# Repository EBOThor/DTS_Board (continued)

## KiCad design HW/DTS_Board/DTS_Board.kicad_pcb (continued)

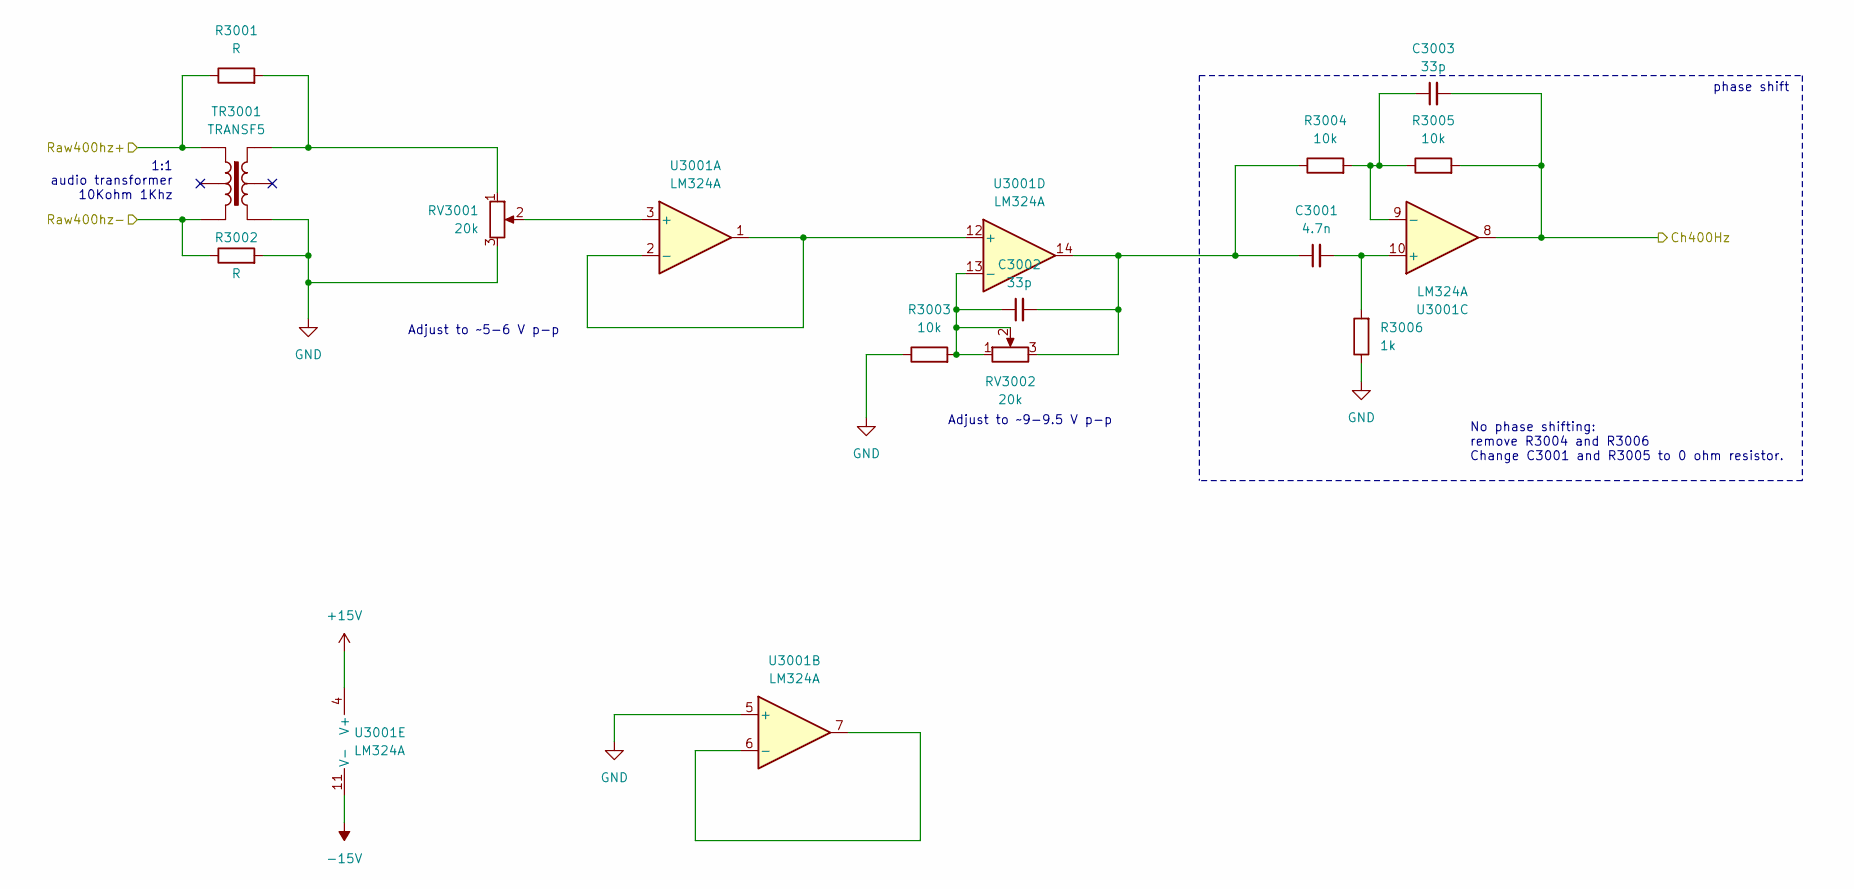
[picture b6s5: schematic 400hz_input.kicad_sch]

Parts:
C3001: 4.7n; C_0805_2012Metric
C3002, C3003: 33p; C_0805_2012Metric
R3001, R3002: R; R_0805_2012Metric
R3003, R3004, R3005: 10k; R_0805_2012Metric
R3006: 1k; R_0805_2012Metric
RV3001, RV3002: 20k; Potentiometer_Bourns_3266W_Vertical
TR3001: TRANSF5; Audio_trafo_6_pin
U3001: LM324A; DIP-14_W7.62mm

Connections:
+15V: U3001.4 (V+); also elsewhere on the board
-15V: U3001.11 (V-); also elsewhere on the board
/400hz_input/Ch400Hz: C3003.2, R3005.2, U3001.8; also elsewhere on the board
/400hz_input/Raw400hz+: R3001.1, TR3001.1; also elsewhere on the board
/400hz_input/Raw400hz-: R3002.1, TR3001.3; also elsewhere on the board
GND: R3002.2, R3003.1, R3006.1, RV3001.3, TR3001.4, U3001.5 (+); also elsewhere on the board
unnamed: C3001.1, C3002.2, R3004.1, RV3002.3, U3001.14
unnamed: R3001.2, RV3001.1, TR3001.6
unnamed: RV3001.2, U3001.3 (+)
unnamed: U3001.1, U3001.2 (-), U3001.12 (+)
unnamed: U3001.6 (-), U3001.7
unnamed: C3001.2, R3006.2, U3001.10 (+)
unnamed: C3003.1, R3004.2, R3005.1, U3001.9 (-)
unnamed: C3002.1, R3003.2, RV3002.1, RV3002.2, U3001.13 (-)

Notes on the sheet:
Adjust to ~9-9.5 V p-p
1:1 audio transformer 10Kohm 1Khz
No phase shifting: remove R3004 and R3006 Change C3001 and R3005 to 0 ohm resistor.
Adjust to ~5-6 V p-p
phase shift

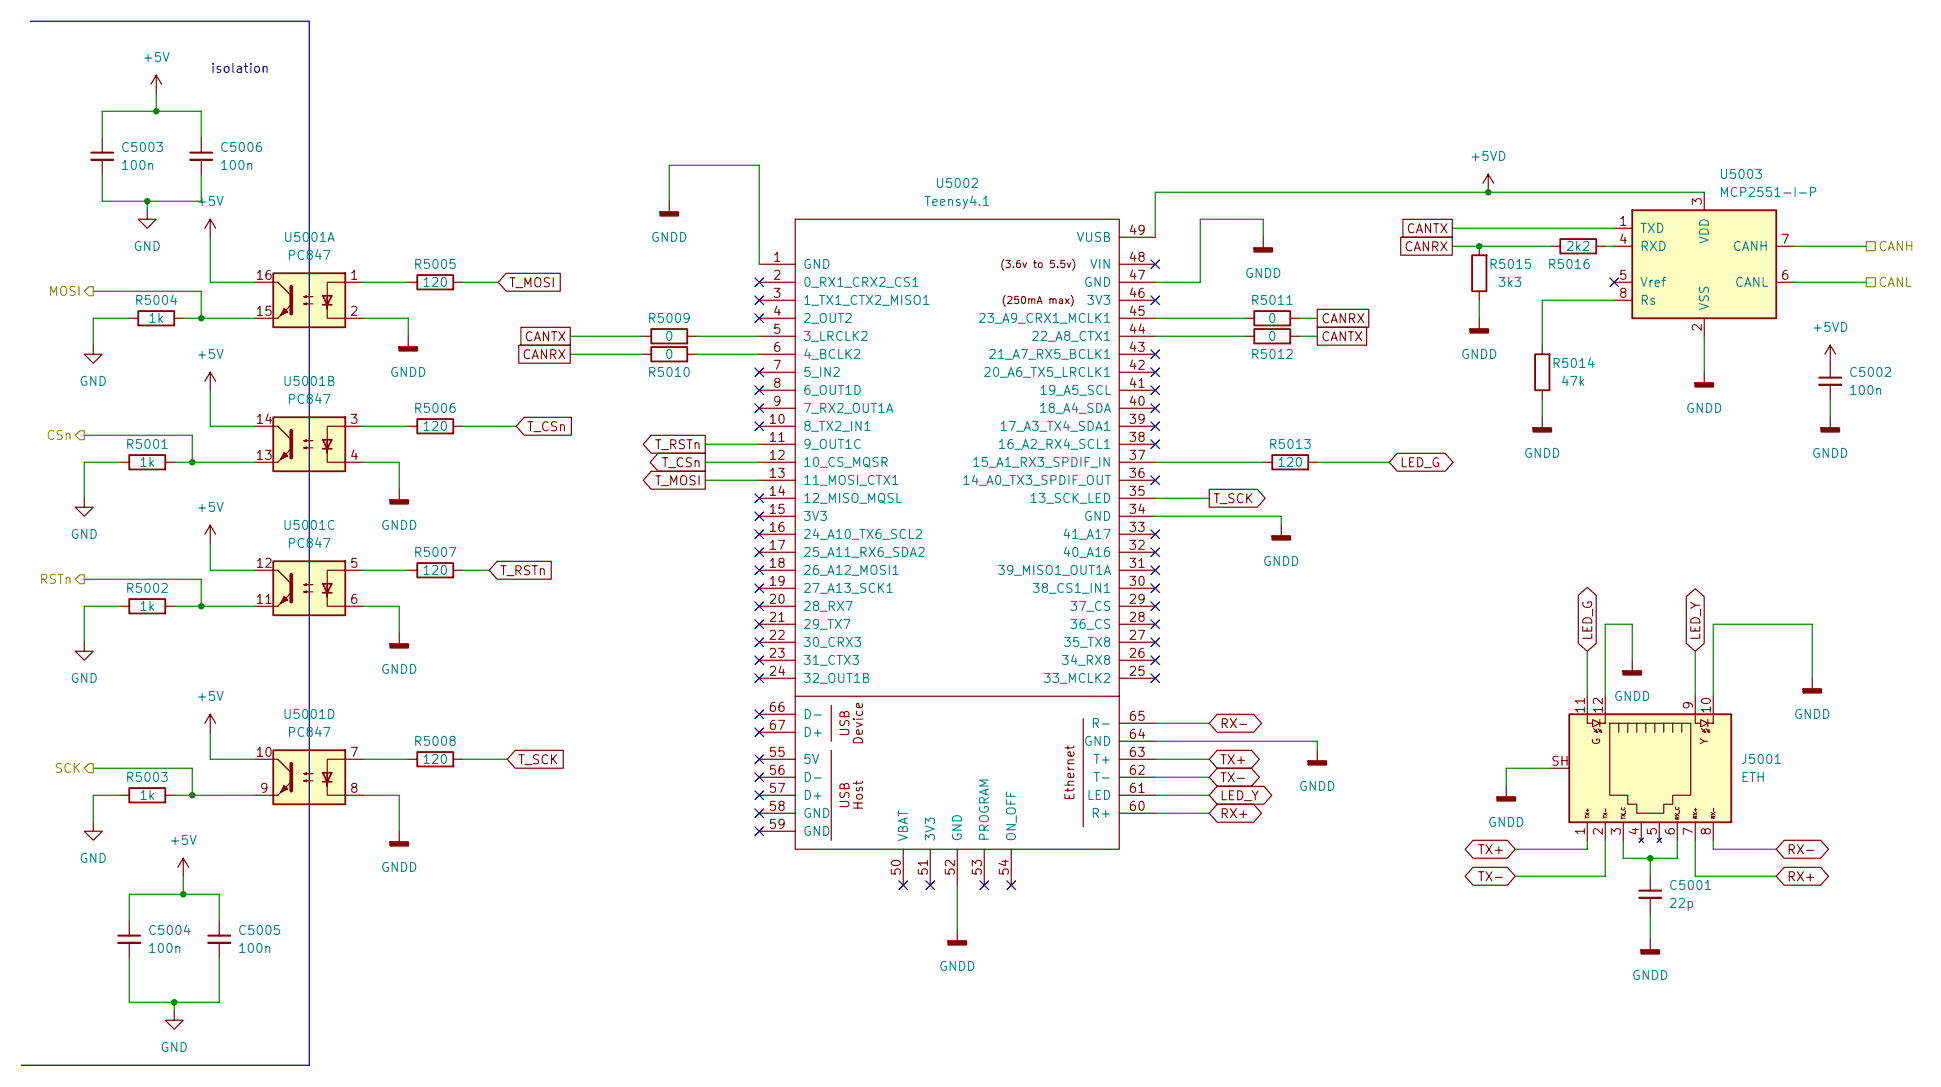
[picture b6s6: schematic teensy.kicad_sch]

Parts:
C5001: 22p; C_0805_2012Metric
C5002, C5003, C5004, C5005, C5006: 100n; C_0805_2012Metric
J5001: ETH; RJ45_LED_Shield
R5001, R5002, R5003, R5004: 1k; R_0805_2012Metric
R5005, R5006, R5007, R5008, R5013: 120; R_0805_2012Metric
R5009, R5010, R5011, R5012: 0; R_0805_2012Metric
R5014: 47k; R_0805_2012Metric
R5015: 3k3; R_0805_2012Metric
R5016: 2k2; R_0805_2012Metric
U5001: PC847; DIP-16_W7.62mm
U5002: Teensy4.1; Teensy41
U5003: MCP2551-I-P; DIP-8_W7.62mm

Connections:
+5V: C5003.1, C5004.1, C5005.1, C5006.1, U5001.10, U5001.12, U5001.14, U5001.16; also elsewhere on the board
+5VD: C5002.1, U5002.49 (VUSB), U5003.3 (VDD)
/LTC1590/CLK: R5003.2, U5001.9; also elsewhere on the board
/LTC1590/CLRn: R5002.2, U5001.11; also elsewhere on the board
/LTC1590/CSn: R5001.2, U5001.13; also elsewhere on the board
/LTC1590/DIN: R5004.2, U5001.15; also elsewhere on the board
/teensy/CANH: U5003.7 (CANH); also elsewhere on the board
/teensy/CANL: U5003.6 (CANL); also elsewhere on the board
CANRX: R5010.1, R5011.2, R5015.2, R5016.1
CANTX: R5009.1, R5012.2, U5003.1 (TXD)
GND: C5003.2, C5004.2, C5005.2, C5006.2, R5001.1, R5002.1, R5003.1, R5004.1; also elsewhere on the board
GNDD: C5001.2, C5002.2, J5001.10, J5001.12, J5001.SH, R5014.1, R5015.1, U5001.2, U5001.4, U5001.6, U5001.8, U5002.1 (GND), U5002.34 (GND), U5002.47 (GND), U5002.52 (GND), U5002.64 (GND), U5003.2 (VSS); also elsewhere on the board
LED_G: J5001.11, R5013.2
LED_Y: J5001.9, U5002.61 (LED)
unnamed: C5001.1, J5001.3, J5001.6
unnamed: R5005.1, U5001.1
unnamed: R5006.1, U5001.3
unnamed: R5007.1, U5001.5
unnamed: R5008.1, U5001.7
unnamed: R5009.2, U5002.5 (3_LRCLK2)
unnamed: R5010.2, U5002.6 (4_BCLK2)
unnamed: R5013.1, U5002.37 (15_A1_RX3_SPDIF_IN)
unnamed: R5012.1, U5002.44 (22_A8_CTX1)
unnamed: R5011.1, U5002.45 (23_A9_CRX1_MCLK1)
unnamed: R5016.2, U5003.4 (RXD)
unnamed: R5014.2, U5003.8 (Rs)
RX+: J5001.7, U5002.60 (R+)
RX-: J5001.8, U5002.65 (R-)
TX+: J5001.1, U5002.63 (T+)
TX-: J5001.2, U5002.62 (T-)
T_CSn: R5006.2, U5002.12 (10_CS_MQSR)
T_MOSI: R5005.2, U5002.13 (11_MOSI_CTX1)
T_RSTn: R5007.2, U5002.11 (9_OUT1C)
T_SCK: R5008.2, U5002.35 (13_SCK_LED)

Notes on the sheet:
isolation

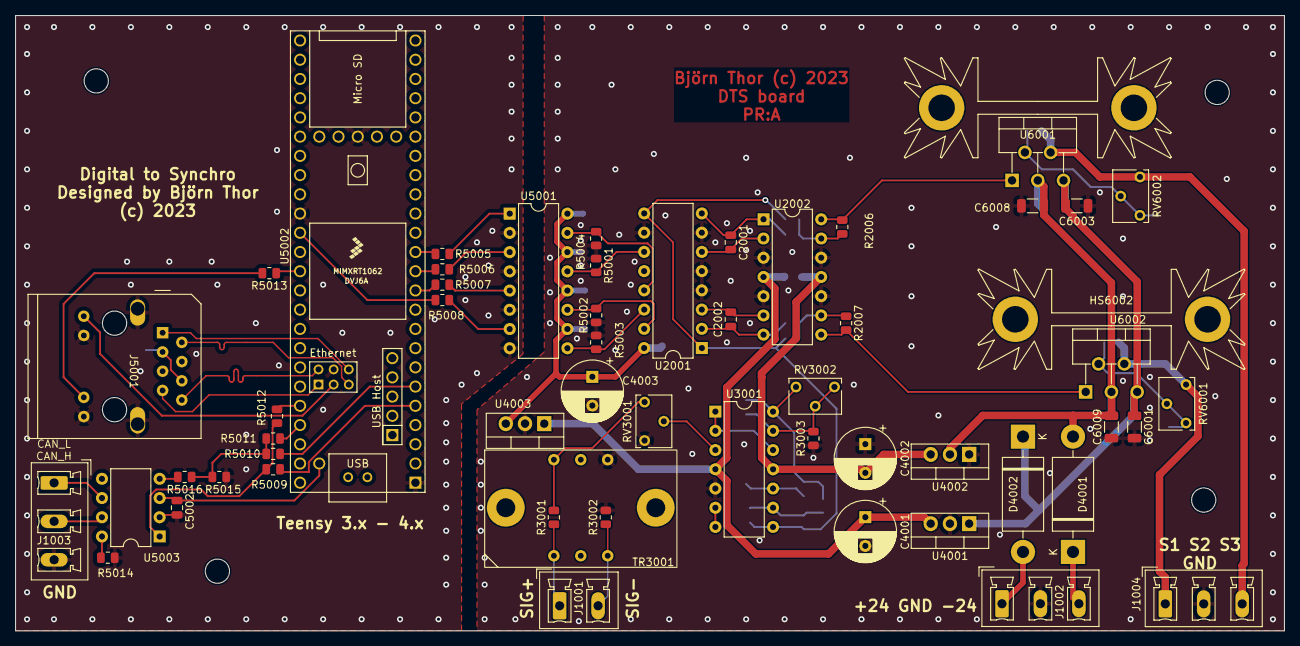
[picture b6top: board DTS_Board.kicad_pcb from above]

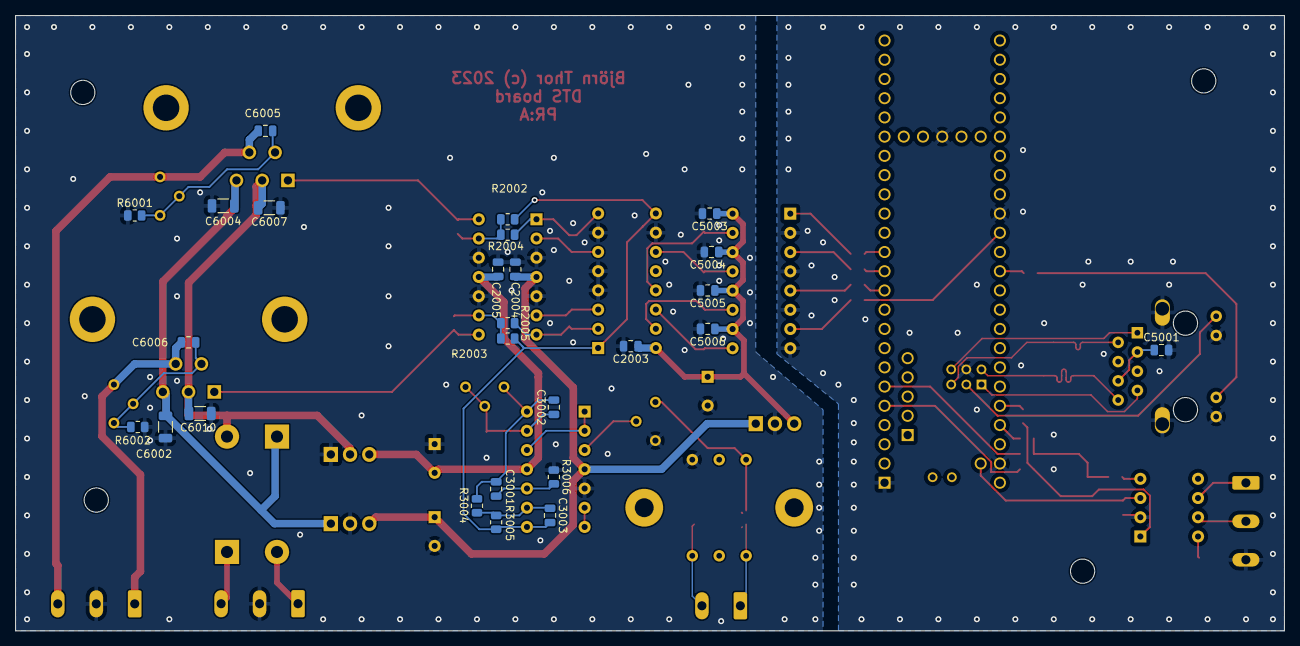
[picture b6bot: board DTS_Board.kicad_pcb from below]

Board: 2 copper layers, 167.6 x 81.3 mm, 82 parts (26 on the bottom side), 63 nets.

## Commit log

2024-11-14 added LISN rev:1
